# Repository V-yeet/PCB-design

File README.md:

STM32F405RGTx microcontroller board

This is the first element of a custom drone to be designed, here is the microcontroller, 
the next iteration will include the other components. 
essentially it is a STM32F405RGTx microcontroller. (shoutout to phils labs)

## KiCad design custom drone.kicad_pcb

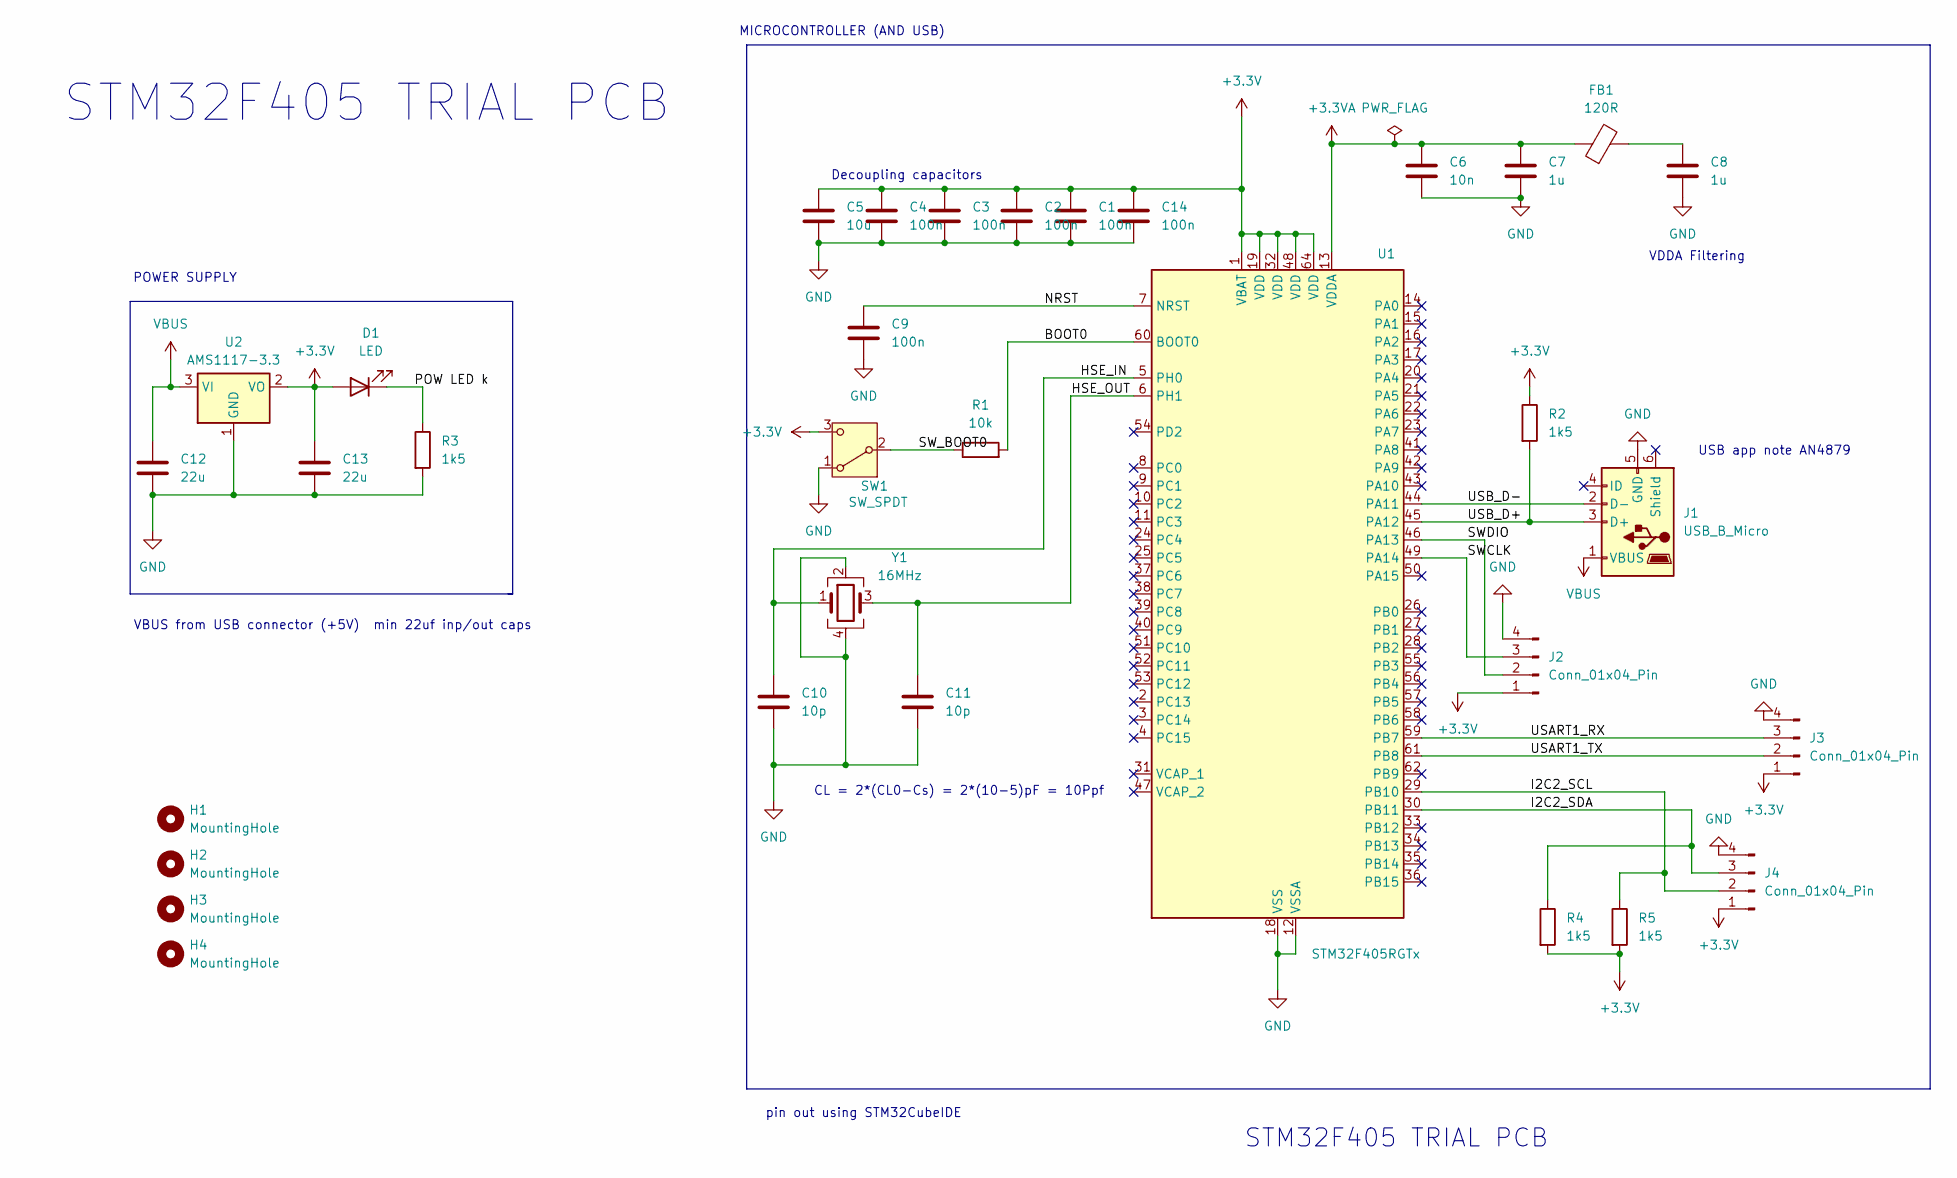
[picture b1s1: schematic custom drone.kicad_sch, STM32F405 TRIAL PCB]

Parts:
C1, C2, C3, C4, C9, C14: 100n; C_0402_1005Metric
C5: 10u; C_0603_1608Metric
C6: 10n; C_0603_1608Metric
C7, C8: 1u; C_0402_1005Metric
C10, C11: 10p; C_0402_1005Metric
C12, C13: 22u; C_0805_2012Metric
D1: LED; LED_0603_1608Metric
FB1: 120R; L_0603_1608Metric
H1, H2, H3, H4: MountingHole; MountingHole_2.2mm_M2
J1: USB_B_Micro; USB_Micro-B_Wuerth_629105150521
J2, J3, J4: Conn_01x04_Pin; PinHeader_1x04_P2.54mm_Vertical
R1: 10k; R_0402_1005Metric
R2, R3, R4, R5: 1k5; R_0402_1005Metric
SW1: SW_SPDT; SW_SPDT_PCM12
U1: STM32F405RGTx; LQFP-64_10x10mm_P0.5mm
U2: AMS1117-3.3; SOT-223-3_TabPin2
Y1: 16MHz; Crystal_SMD_3225-4Pin_3.2x2.5mm

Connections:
+3.3V: C1.1, C2.1, C3.1, C4.1, C5.1, C13.1, C14.1, D1.2 (A), J2.1, J3.1, J4.1, R2.1, R4.2, R5.2, SW1.3 (C), U1.1 (VBAT), U1.19 (VDD), U1.32 (VDD), U1.48 (VDD), U1.64 (VDD), U2.2 (VO)
+3.3VA: C6.1, C7.1, FB1.1, U1.13 (VDDA)
/BOOT0: R1.2, U1.60 (BOOT0)
/HSE_IN: C10.1, U1.5 (PH0), Y1.1
/HSE_OUT: C11.1, U1.6 (PH1), Y1.3
/I2C2_SCL: J4.2, R5.1, U1.29 (PB10)
/I2C2_SDA: J4.3, R4.1, U1.30 (PB11)
/NRST: C9.1, U1.7 (NRST)
/POW LED k: D1.1 (K), R3.1
/SWCLK: J2.3, U1.49 (PA14)
/SWDIO: J2.2, U1.46 (PA13)
/SW_BOOT0: R1.1, SW1.2 (B)
/USART1_RX: J3.3, U1.59 (PB7)
/USART1_TX: J3.2, U1.61 (PB8)
/USB_D+: J1.3 (D+), R2.2, U1.45 (PA12)
/USB_D-: J1.2 (D-), U1.44 (PA11)
GND: C1.2, C2.2, C3.2, C4.2, C5.2, C6.2, C7.2, C8.2, C9.2, C10.2, C11.2, C12.2, C13.2, C14.2, J1.5 (GND), J2.4, J3.4, J4.4, R3.2, SW1.1 (A), U1.12 (VSSA), U1.18 (VSS), U1.63 (VSS), U2.1 (GND), Y1.2, Y1.4
unnamed: C8.1, FB1.2
VBUS: C12.1, J1.1 (VBUS), U2.3 (VI)

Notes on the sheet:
CL = 2*(CL0-Cs) = 2*(10-5)pF = 10Ppf
pin out using STM32CubeIDE
Decoupling capacitors
VDDA Filtering
STM32F405 TRIAL PCB
USB app note AN4879
VBUS from USB connector (+5V) min 22uf inp/out caps
POWER SUPPLY
MICROCONTROLLER (AND USB)

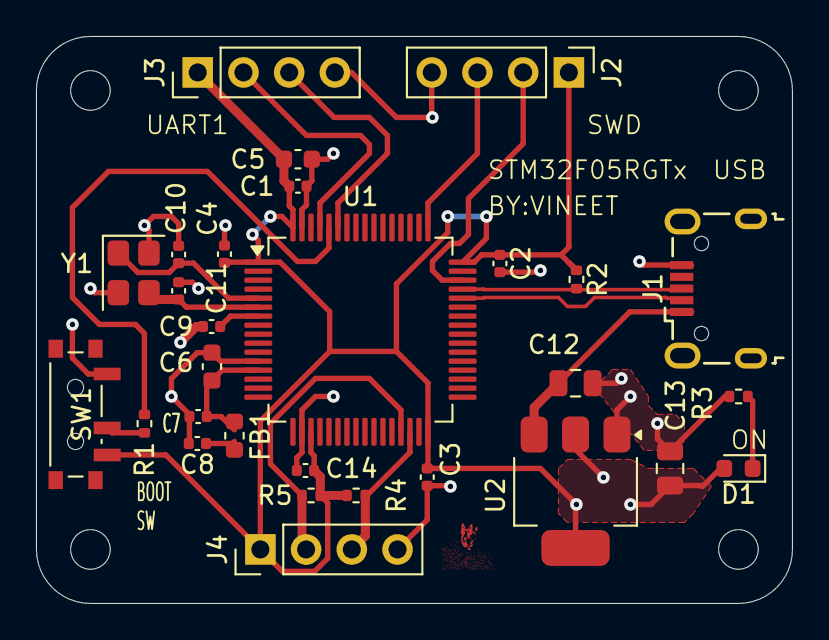
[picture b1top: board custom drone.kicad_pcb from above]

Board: 2 copper layers, 42.0 x 31.5 mm, 33 parts (0 on the bottom side), 19 nets.
